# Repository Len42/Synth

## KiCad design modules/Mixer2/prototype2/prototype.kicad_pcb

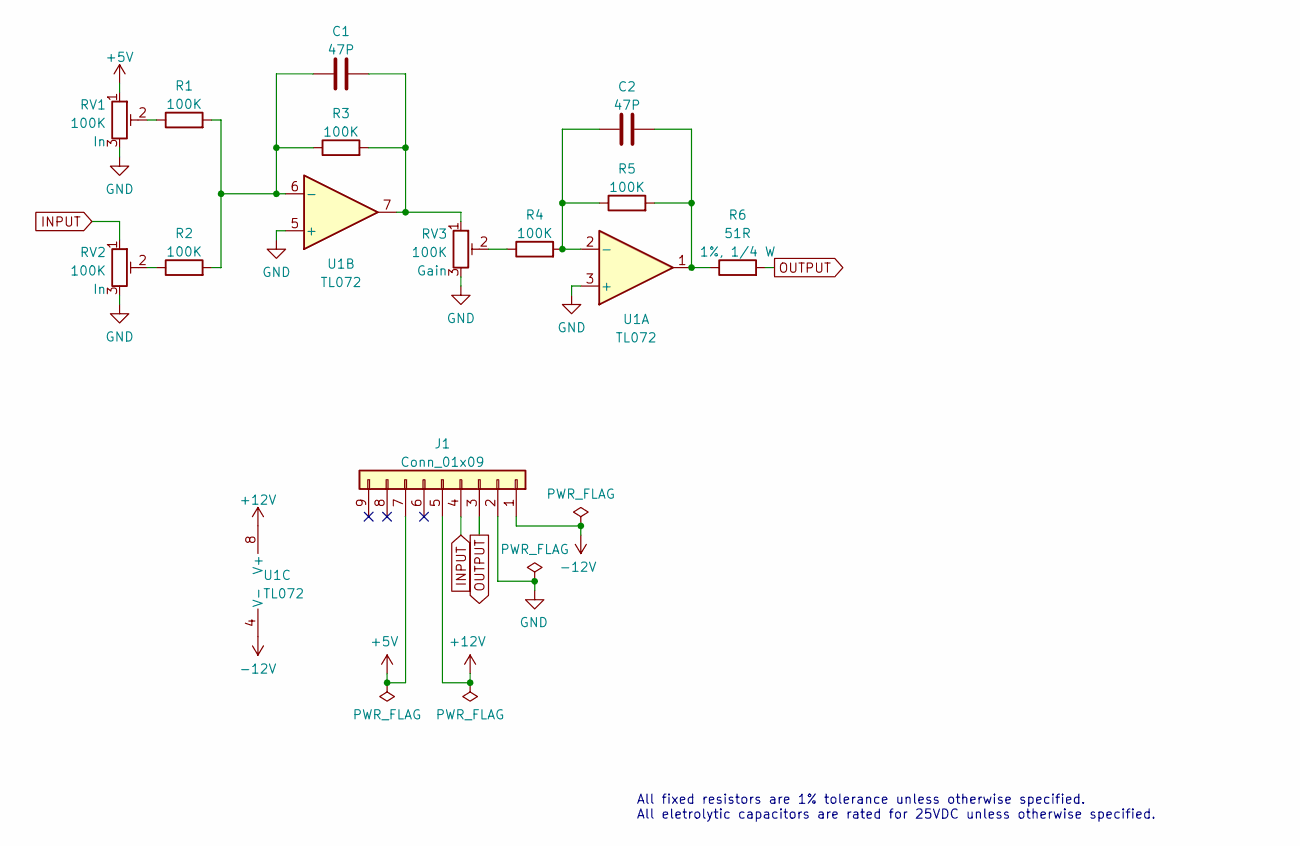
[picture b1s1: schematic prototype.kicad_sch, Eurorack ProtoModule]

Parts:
C1, C2: 47P; C_Disc_D5.0mm_W2.5mm_P2.50mm
J1: Conn_01x09; PinHeader_1x09_P2.54mm_Vertical
R1, R2, R3, R4, R5: 100K; R_Axial_DIN0207_L6.3mm_D2.5mm_P7.62mm_Horizontal; ManufacturerPartNum MFR-12*
R6: 51R; R_Axial_DIN0207_L6.3mm_D2.5mm_P10.16mm_Horizontal; ManufacturerPartNum MFR-25FBF52-51R
RV1, RV2, RV3: 100K; Potentiometer_Bourns_3386P_Top; ManufacturerPartNum 3386*
U1: TL072; DIP-8_W7.62mm; ManufacturerPartNum TL072BCP

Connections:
+5V: J1.7, RV1.1
+12V: J1.5, U1.8 (V+)
-12V: J1.1, U1.4 (V-)
GND: J1.2, RV1.3, RV2.3, RV3.3, U1.3 (+), U1.5 (+)
INPUT: J1.4, RV2.1
unnamed: C1.1, R1.2, R2.2, R3.1, U1.6 (-)
unnamed: C1.2, R3.2, RV3.1, U1.7
unnamed: C2.1, R4.2, R5.1, U1.2 (-)
unnamed: C2.2, R5.2, R6.1, U1.1
unnamed: R1.1, RV1.2
unnamed: R2.1, RV2.2
unnamed: R4.1, RV3.2
OUTPUT: J1.3, R6.2

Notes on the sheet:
All fixed resistors are 1% tolerance unless otherwise specified. All eletrolytic capacitors are rated for 25VDC unless otherwise specified.

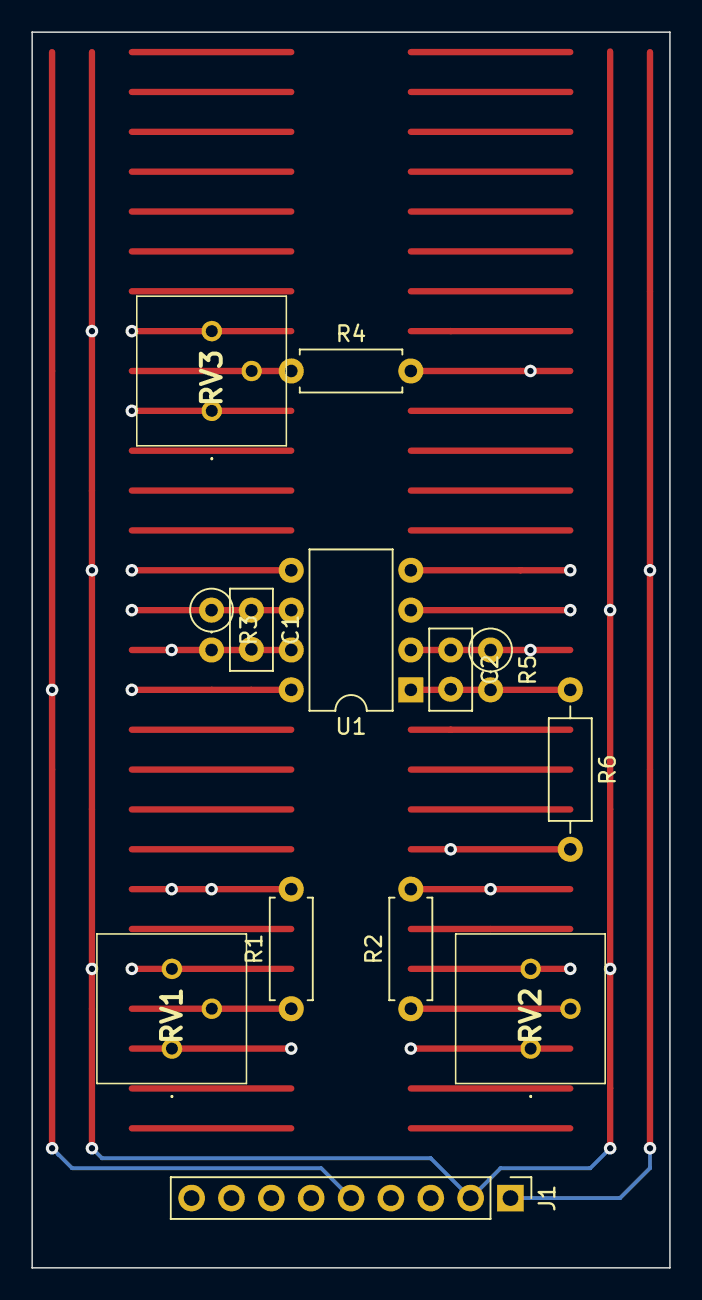
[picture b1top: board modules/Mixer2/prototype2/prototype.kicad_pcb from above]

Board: 6 copper layers, 40.6 x 78.7 mm, 13 parts (0 on the bottom side), 13 nets.

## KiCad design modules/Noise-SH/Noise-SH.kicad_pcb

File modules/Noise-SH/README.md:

# Noise / Sample & Hold

## 4HP Eurorack Module

### Features
- White and pink(ish) noise output
- Sample-and-hold with variable slew rate
- S&H can be triggered by an internal clock or external input
- Internal clock is output on the trigger jack when selected

### Notes

This module is built using the [Delptronics Module Construction Set](https://delptronics.com/module-construction-set.php) which includes PCBs for the front panel controls and other components. The PCB layout file is just a guide showing how I placed the components on the Delptronics boards. (It's a bit of a mess - sorry!)

Please note that I am a hobbyist, not a trained electronics engineer. No guarantees!

### Acknowledgements

[synthnerd](https://synthnerd.wordpress.com/2020/03/09/synth-diy-a-white-noise-generator/)

[Mutable Instruments](https://mutable-instruments.net/modules/kinks/open_source/)

### Software Used

[KiCad](https://www.kicad.org/) 5.1.10-1

<hr /><div><div style="float:left; padding-right:10px;"></div><div style="padding-left:10px;">© 2022 Len Popp<br />This work is licensed under a <a rel="license" href="http://creativecommons.org/licenses/by-sa/4.0/">Creative Commons Attribution-ShareAlike 4.0 International License</a>.</div></div>

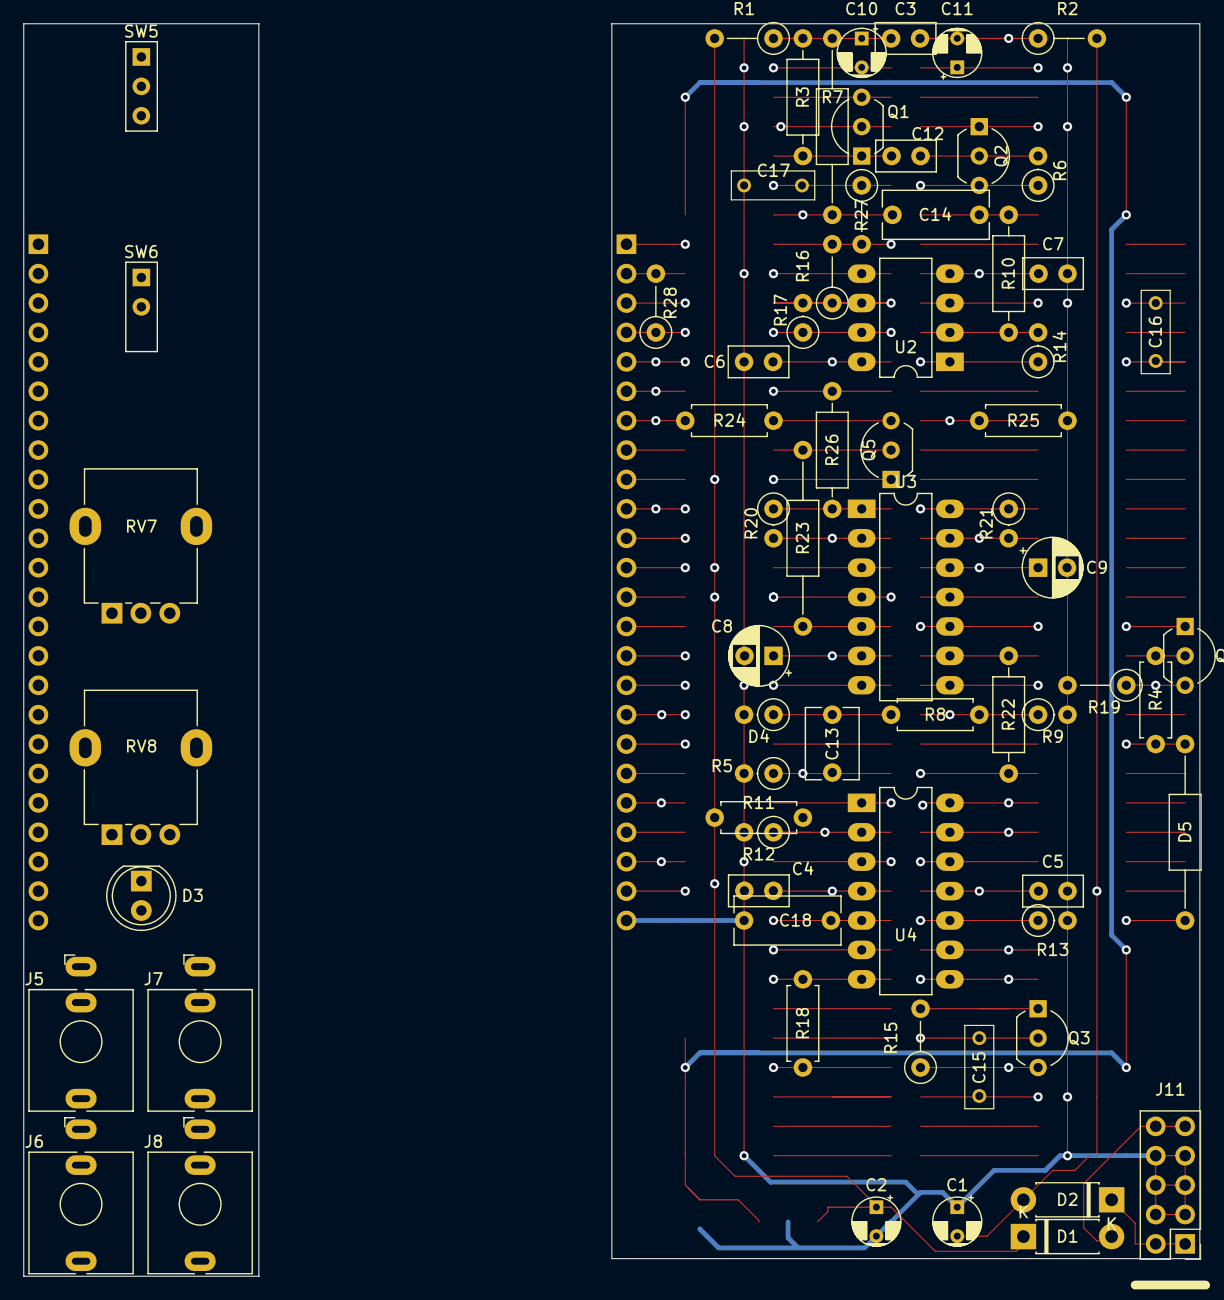
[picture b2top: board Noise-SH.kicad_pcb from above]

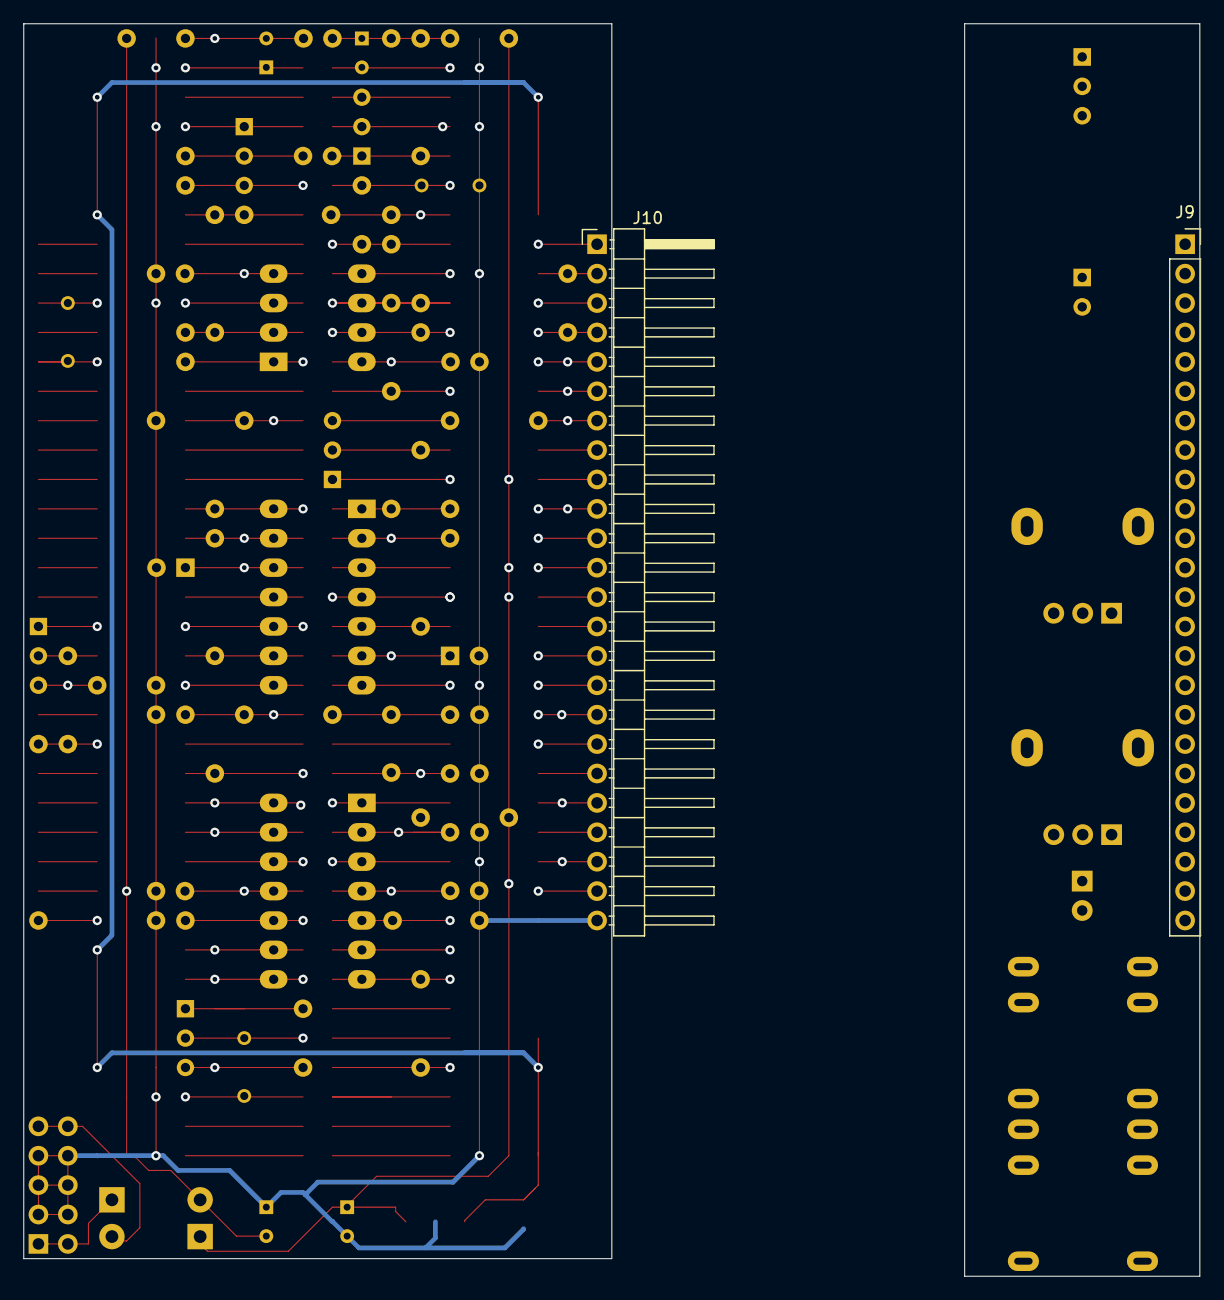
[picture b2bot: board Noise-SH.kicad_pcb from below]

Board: 6 copper layers, 50.8 x 106.7 mm, 70 parts (2 on the bottom side), 61 nets.

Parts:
C1, C2, C10, C11: 10U; CP_Radial_D4.0mm_P2.50mm
C3, C4, C5, C6, C7, C12: 100N; C_Disc_D5.0mm_W2.5mm_P2.50mm
C8: 4U7; CP_Radial_D5.0mm_P2.50mm
C9: 1U; CP_Radial_D5.0mm_P2.50mm
C13: 100P; C_Disc_D6.0mm_W4.4mm_P5.00mm
C14, C18: 1U; C_Rect_L9.0mm_W4.0mm_P7.50mm_MKT
C15, C16: 10N; C_Rect_Kemet_L7.2mm_W2.5mm_P5mm
C17: 1N; C_Rect_Kemet_L7.2mm_W2.5mm_P5mm
D1, D2: MBR150; D_DO-41_SOD81_P7.62mm_Horizontal
D3: LED_5mm_Blue; LED_D5.0mm
D4: 1N4148; SB_Gen_1
D5: 1N4148; SB_Gen_6
J5, J6, J7, J8: WQP-PJ398SM; Jack_3.5mm_QingPu_WQP-PJ398SM_Vertical
J9: Conn_Front; PinSocket_Delptronics_Front
J10: Conn__Back; PinHeader_Delptronics_Back_Left_4HP
J11: Eurorack_10; PinHeader-Eurorack-10-TH
Q1, Q2: 2N3904; TO-92_Inline_Wide
Q3: J309; TO-92_Inline_Wide
Q4, Q5: 2N3906; TO-92_Inline_Wide
R1, R2: 10R; SB_Gen_2
R3: 220K; R_Axial_DIN0207_L6.3mm_D2.5mm_P10.16mm_Horizontal
R4: 10K; R_Axial_DIN0207_L6.3mm_D2.5mm_P7.62mm_Horizontal
R5, R14: 100K; SB_Gen_1
R6, R13: 1M; SB_Gen_1
R7: 4K7; SB_Gen_6
R8: 11K; R_Axial_DIN0207_L6.3mm_D2.5mm_P7.62mm_Horizontal
R9: 330K; SB_Gen_1
R10: 15K; SB_Gen_4
R11: 1M; R_Axial_DIN0207_L6.3mm_D2.5mm_P7.62mm_Horizontal
R12: 120K; SB_Gen_1
R15: 1M; SB_Gen_2
R16, R19: 10K; SB_Gen_2
R17: 10K; SB_Gen_1
R18: 1K; R_Axial_DIN0207_L6.3mm_D2.5mm_P7.62mm_Horizontal
R20: 1K5; SB_Gen_1
R21: 82K; SB_Gen_1
R22: 2K2; R_Axial_DIN0207_L6.3mm_D2.5mm_P10.16mm_Horizontal
R23: 10K; SB_Gen_6
R24: 6K2; R_Axial_DIN0207_L6.3mm_D2.5mm_P7.62mm_Horizontal
R25: 13K; R_Axial_DIN0207_L6.3mm_D2.5mm_P7.62mm_Horizontal
R26: 4K7; R_Axial_DIN0207_L6.3mm_D2.5mm_P10.16mm_Horizontal
R27: 3K9; SB_Gen_2
R28: 1K; SB_Gen_2
RV7, RV8: 1M; Potentiometer_Alpha_RD901F-40-00D_Single_Vertical
SW5: ON_ON; SW_SPDT_THT_2.54
SW6: SPST; SW_SPST_THT_2.54
U2: TL072; DIP-8_W7.62mm_LongPads
U3: ICM7556; DIP-14_W7.62mm_LongPads
U4: TL074; DIP-14_W7.62mm_LongPads

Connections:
+12VA: C3.1, C6.1, C10.1, R1.1, R3.1, R7.1, U2.8
-12V: C1.2, C5.2, D1.2, R2.2, U4.11
-12VA: C3.2, C7.2, C11.2, R2.1, U2.4
/Main/TRIGGER: D5.1, R4.2, U4.1
IN-SAMPLE: J10.5, R13.1, U4.10
INOUT-TRIG: C13.2, J10.6, J10.15, R5.1
LED-TRIG-A: J10.23, R22.1
LED-TRIG-C: C1.1, C2.2, C4.2, C5.1, C6.2, C7.1, C8.2, C9.2, C10.2, C11.1, C15.2, C17.2, C18.1, D4.2, J5.S, J6.S, J7.S, J8.S, J9.24, J10.22, J10.24, J11.3, J11.4, J11.5, J11.6, J11.7, J11.8, Q1.2, Q2.1, R5.2, R9.2, R12.2, R13.2, R19.2, R25.2, U2.3, U2.5, U3.7
NOISE-SELECT: J10.2, R28.2
unnamed: C8.1, R20.2, U3.2, U3.6
unnamed: C9.1, R21.2, U3.12, U3.13
unnamed: C12.1, Q2.2, R6.2
unnamed: C12.2, Q1.1, R3.2
unnamed: C13.1, D4.1, R8.2
unnamed: C14.1, R10.2
unnamed: C14.2, Q2.3, R6.1, R7.2
unnamed: C15.1, Q3.2, U4.12
unnamed: C16.2, R16.1, R17.2, U2.6
unnamed: D1.1, J11.1, J11.2
unnamed: D2.2, J11.9, J11.10
unnamed: D3.1, J9.22
unnamed: D3.2, J9.23
unnamed: D5.2, Q3.3, R15.1
unnamed: J5.T, J9.5
unnamed: J5.TN, J9.4
unnamed: J6.T, J9.10
unnamed: J7.T, J9.15
unnamed: J8.T, J9.20
unnamed: J9.1, SW5.3
unnamed: J9.2, SW5.2
unnamed: J9.3, SW5.1
unnamed: J9.6, SW6.1
unnamed: J9.7, SW6.2
unnamed: J9.11, RV7.3
unnamed: J9.12, RV7.2
unnamed: J9.13, RV7.1
unnamed: J9.16, RV8.3
unnamed: J9.17, RV8.2
unnamed: J9.18, RV8.1
unnamed: Q3.1, R15.2, U4.8, U4.9
unnamed: Q4.2, R4.1
unnamed: Q4.3, R19.1, U3.8
unnamed: Q5.2, R23.1
unnamed: Q5.3, R24.1
unnamed: R8.1, R9.1, U4.3
unnamed: R10.1, R14.2, U2.2
unnamed: R11.2, R12.1, U4.2
unnamed: R14.1, R16.2, R27.2, U2.1
unnamed: R18.2, U4.6, U4.7
unnamed: R20.1, R26.2, U3.1
unnamed: R22.2, U3.9
unnamed: R23.2, U3.5
OUT-CLOCK-TRIG: J10.7, R24.2, R25.1
OUT-HOLD: J10.10, R18.1
OUT-NOISE: J10.4, J10.20, R28.1
OUT-NOISE-PINK: C16.1, J10.1, R17.1, U2.7
OUT-NOISE-WHITE: C17.1, J10.3, R27.1
RV-CLOCK-FREQ-1: C2.1, C4.1, D2.1, J10.12, Q4.1, Q5.1, R1.2, R11.1, R21.1, U3.4, U3.10, U3.14, U4.4
RV-CLOCK-FREQ-2: J10.11, R26.1
RV-SLEW-1: J10.18, U4.13, U4.14
RV-SLEW-2: C18.2, J10.16, J10.17, U4.5

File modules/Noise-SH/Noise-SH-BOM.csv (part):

Ref,Qty,Name,Value,Value2,Note,Description,Datasheet,Manufacturer,ManuPartNum,Distributor1,DistributorPartNum1,DistributorPartLink1,Distributor2,DistributorPartNum2,DistributorPartLink2,Distributor3,DistributorPartNum3,DistributorPartLink3
"C1 C2 C10 C11","4","CP_10U","10U","25 VDC","","Capacitor - Electrolytic - 12 V decoupling","https://industrial.panasonic.com/cdbs/www-data/pdf/RDF0000/A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","Panasonic","EEA-FC1E100","Mouser","667-EEA-FC1E100","https://www.mouser.ca/ProductDetail/Panasonic/EEA-FC1E100?qs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"
"C3 C4 C5 C6 C7","5","CC_100N","100N","","IC decoupling","Capacitor - Ceramic - IC decoupling","https://product.tdk.com/system/files/dam/doc/product/capacit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","TDK","FG18X7R1H104KNT06","Mouser","810-FG18X7R1H104KNT6","https://www.mouser.ca/ProductDetail/810-FG18X7R1H104KNT6"
"C8","1","CP","4U7","","","Capacitor - Electrolytic","https://www.mouser.ca/datasheet/2/977/e_YXJ-1601195.pdf","Rubycon","50YXJ1M5X11","Mouser","232-50YXJ1M5X11","https://www.mouser.ca/ProductDetail/232-50YXJ1M5X11"
"C9","1","CP","1U","","","Capacitor - Electrolytic","https://www.mouser.ca/datasheet/2/977/e_YXJ-1601195.pdf","Rubycon","50YXJ1M5X11","Mouser","232-50YXJ1M5X11","https://www.mouser.ca/ProductDetail/232-50YXJ1M5X11"
"C12","1","C","100N","C0G/NP0","","Capacitor - Unpolarized","https://product.tdk.com/system/files/dam/doc/product/capacit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","TDK","FA16C0G2A104JRU06","Mouser","810-FA16C0G2A104JRU6","https://www.mouser.ca/ProductDetail/TDK/FA16C0G2A104JRU06?qs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"
"C13","1","C","100P","","","Capacitor - Unpolarized","https://www.mouser.com/catalog/specsheets/tdkc-s-a0002934059-1.pdf","TDK","CK45-R3AD101K-NRA","Mouser","810-CK45-R3AD101K-NA","https://www.mouser.ca/ProductDetail/TDK/CK45-R3AD101K-NRA?qs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"
"C14 C18","2","C","1U","","","Capacitor - Unpolarized","https://product.tdk.com/system/files/dam/doc/product/capacit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","TDK","B32560J0105K000","Mouser","871-B32560J105K","https://www.mouser.ca/ProductDetail/EPCOS-TDK/B32560J0105K00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"
"C15 C16","2","CF","10N","","","Capacitor - Film","https://www.mouser.ca/datasheet/2/212/1/KEM_F3072_SMR-1103375.pdf","KEMET","SMR5103J50J01L16.5CBULK","Mouser","80-SMR5103J50J0116","https://www.mouser.ca/ProductDetail/?qs=lyRJTFulC0ZVzsb1DGnF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"
"C17","1","CF","1N","","","Capacitor - Film","https://www.mouser.ca/datasheet/2/212/F3294_MMK-1101858.pdf","KEMET","MMK5102J100J01L16.5TA18","Mouser","80-MMK5102J100J1TA18","https://www.mouser.ca/ProductDetail/80-MMK5102J100J1TA18"
"D1 D2","2","MBR150","MBR150","","","Schottky rectifier diode","https://www.onsemi.com/pdf/datasheet/mbr150-d.pdf","On Semi","MBR150RLG","Mouser","863-MBR150RLG","https://www.mouser.ca/ProductDetail/ON-Semiconductor/MBR150R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"
"D3","1","LED_5mm_Blue","LED_5mm_Blue","","","Blue Light Emitting Diode","https://www.mouser.ca/datasheet/2/423/VAOL-5LSBY1-1064871.pdf","VCC","VAOL-5LSBY1","Mouser","593-VAOL-5LSBY1","https://www.mouser.ca/ProductDetail/VCC/VAOL-5LSBY1?qs=sGAEp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"
"D4 D5","2","1N4148","1N4148","","","Switching diode, 100V 0.15A, DO-35","https://www.mouser.ca/datasheet/2/308/1N914_D-2309448.pdf","On Semi / Fairchild","1N4148-T50R","Mouser","512-1N4148T50R","https://www.mouser.ca/ProductDetail/?qs=0lQeLiL1qyZS6rosZp7E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"
"H1","1","PCB_Delptronics_MCS_4HP","PCB_Delptronics_MCS_4HP","","PCB & panel kit","Delptronics Module Construction Set - 4HP PCB & panel kit","https://delptronics.com/module-construction-set.php","Delptronics","","Delptronics","","https://delptronics.com/module-construction-set.php","synthCube","DELPMCSMSTR","https://synthcube.com/cart/delptronics-module-construction-set","Modular Addict","","https://modularaddict.com/module-construction-set-eurorack-p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"
"J5 J6 J7 J8","4","Jack_WQP-PJ398","WQP-PJ398SM","","","Audio Jack, 2 Poles (Mono / TS), Switched T Pole (Normalling), QingPu / Thonkiconn","http://www.qingpu-electronics.com/en/products/WQP-PJ398SM-362.html","QingPu / Thonk","PJ398SM / WQP518MA","Thonk","PJ398SM","https://www.thonk.co.uk/shop/thonkiconn/","SynthCube","WQP518MA","https://synthcube.com/cart/3-5mm-euro-jacks","Adafruit","4031","https://www.adafruit.com/product/4031"
"Q1 Q2","2","Q_NPN_2N3904","2N3904","","","Small Signal NPN Transistor, 0.2A Ic, 40V Vce, TO-92","https://www.onsemi.com/pub/Collateral/2N3903-D.PDF","Central Semiconductor","2N3904 PBFREE","Mouser","610-2N3904","https://www.mouser.ca/ProductDetail/Central-Semiconductor/2N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"
"Q3","1","Q_JFET_N_SDG","J309","","","N-JFET transistor, source/drain/gate","https://www.mouser.ca/datasheet/2/676/jfet-j308-j309-j310-in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","InterFET","J309","Mouser","106-J309","https://www.mouser.ca/ProductDetail/InterFET/J309?qs=%2Fha2p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"
"Q4 Q5","2","Q_PNP_2N3906","2N3906","","","Small Signal PNP Transistor, -0.2A Ic, -40V Vce, TO-92","https://www.onsemi.com/pub/Collateral/2N3906-D.PDF","ON Semiconductor / Fairchild","2N3906TAR","Mouser","512-2N3906TAR","https://www.mouser.ca/ProductDetail/ON-Semiconductor-Fairchi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"
"R1 R2","2","R","10R","","","Resistor","https://www.mouser.ca/datasheet/2/447/Yageo_LR_MFR_1-1714151.pdf","Mouser","MFR-25FTF52-10R","Mouser","603-MFR-25FTF52-10R","https://www.mouser.ca/ProductDetail/YAGEO/MFR-25FTF52-10R?qs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"
"R3","1","R","220K","","","Resistor","https://www.mouser.ca/datasheet/2/447/Yageo_LR_MFR_1-1714151.pdf","YAGEO","MFR-25FTF52-220K","Mouser","603-MFR-25FTF52-220K","https://www.mouser.ca/ProductDetail/?qs=iCzJi%2FIZBF5PYwecy8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"
"R4 R16 R17 R19 R23","5","R","10K","","","Resistor","https://www.mouser.ca/datasheet/2/447/Yageo_LR_MFR_1-1714151.pdf","YAGEO","MFR-12FRF52-10K","Mouser","603-MFR-12FRF5210K","https://www.mouser.ca/ProductDetail/?qs=19cKSROHwrBLAZVjkXso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"
"R5 R14","2","R","100K","","","Resistor","https://www.mouser.ca/datasheet/2/447/Yageo_LR_MFR_1-1714151.pdf","YAGEO","MFR-12FTF52-100K","Mouser","603-MFR-12FTF52-100K","https://www.mouser.ca/ProductDetail/YAGEO/MFR-12FTF52-100K?q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"
"R6 R11 R13 R15","4","R","1M","","","Resistor","https://www.mouser.ca/datasheet/2/447/Yageo_LR_MFR_1-1714151.pdf","YAGEO","MFR-12FTF52-1M","Mouser","603-MFR-12FTF52-1M","https://www.mouser.ca/ProductDetail/YAGEO/MFR-12FTF52-1M?qs=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"
"R7 R26","2","R","4K7","","","Resistor","https://www.mouser.ca/datasheet/2/447/Yageo_LR_MFR_1-1714151.pdf","YAGEO","MFR-12FTF52-4K7","Mouser","603-MFR-12FTF52-4K7","https://www.mouser.ca/ProductDetail/YAGEO/MFR-12FTF52-4K7?qs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"
"R8","1","R","11K","","","Resistor","https://www.mouser.ca/datasheet/2/447/Yageo_LR_MFR_1-1714151.pdf","YAGEO","MFR-12FTF52-11K","Mouser","603-MFR-12FTF52-11K","https://www.mouser.ca/ProductDetail/YAGEO/MFR-12FTF52-11K?qs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"
"R9","1","R","330K","","","Resistor","https://www.mouser.ca/datasheet/2/447/Yageo_LR_MFR_1-1714151.pdf","YAGEO","MFR-12FTF52-100K","Mouser","603-MFR-12FTF52-100K","https://www.mouser.ca/ProductDetail/YAGEO/MFR-12FTF52-100K?q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"
"R10","1","R","15K","","","Resistor","https://www.mouser.ca/datasheet/2/447/Yageo_LR_MFR_1-1714151.pdf","YAGEO","MFR-12FTF52-24K","Mouser","603-MFR-12FTF52-24K","https://www.mouser.ca/ProductDetail/YAGEO/MFR-12FTF52-24K?qs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"
"R12","1","R","120K","","","Resistor","https://www.mouser.ca/datasheet/2/447/Yageo_LR_MFR_1-1714151.pdf","YAGEO","MFR-25FTE52-15K","Mouser","603-MFR-25FTE52-15K","https://www.mouser.ca/ProductDetail/YAGEO/MFR-25FTE52-15K?qs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"
"R18 R28","2","R_1K_Output","1K","5%, 1/4 W","Output limiting","Resistor","https://www.mouser.ca/datasheet/2/427/ccf07-1762725.pdf","Vishay / Dale","CCF071K00JKE36","Mouser","71-CCF071K00JKE36","https://www.mouser.ca/ProductDetail/Vishay-Dale/CCF071K00JKE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"
"R20","1","R","1K5","","","Resistor","https://www.mouser.ca/datasheet/2/447/Yageo_LR_MFR_1-1714151.pdf","YAGEO","MFR-12*","Mouser","603-MFR-12*","https://www.mouser.ca/c/?m=YAGEO&power+rating=166+mW+(1%2f6+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"
"R21","1","R","82K","","","Resistor","https://www.mouser.ca/datasheet/2/447/Yageo_LR_MFR_1-1714151.pdf","YAGEO","MFR-12*","Mouser","603-MFR-12*","https://www.mouser.ca/c/?m=YAGEO&power+rating=166+mW+(1%2f6+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"
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
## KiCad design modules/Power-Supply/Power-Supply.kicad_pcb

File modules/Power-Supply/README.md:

# Eurorack Power Supply

This is the power supply that I made for my Eurorack modular system. It is meant to live inside the system case with the power switch and DC input jack mounted on the side of the case.

### Specs

Input: Requires between 9 V and 36 V DC, 35W (from a power brick / wall wart / laptop charger)

Output: +12 V, -12 V (1 A each), +5 V (500 mA)

### Notes

I used an old laptop charger as the AC-DC converter (power brick) so I didn't have to mess around with mains voltage. The required Eurorack voltages (+12 V, -12 V, +5 V) are supplied by switching DC-DC converters. The outputs are isolated from the input.

There are two 16-pin Eurorack power connectors; you'll want a busboard or flying-bus cable to feed multiple modules.

The power supply is assembled on a stripboard PCB. I have provided a layout diagram.

Please note that I am a hobbyist, not a trained electronics engineer. No guarantees!

### Software Used

[KiCad](https://www.kicad.org/) 6.0.0

<hr /><br />© 2022 Len Popp CC BY<br />This work is licensed under a <a rel="license" href="http://creativecommons.org/licenses/by/4.0/">Creative Commons Attribution 4.0 International License</a>.

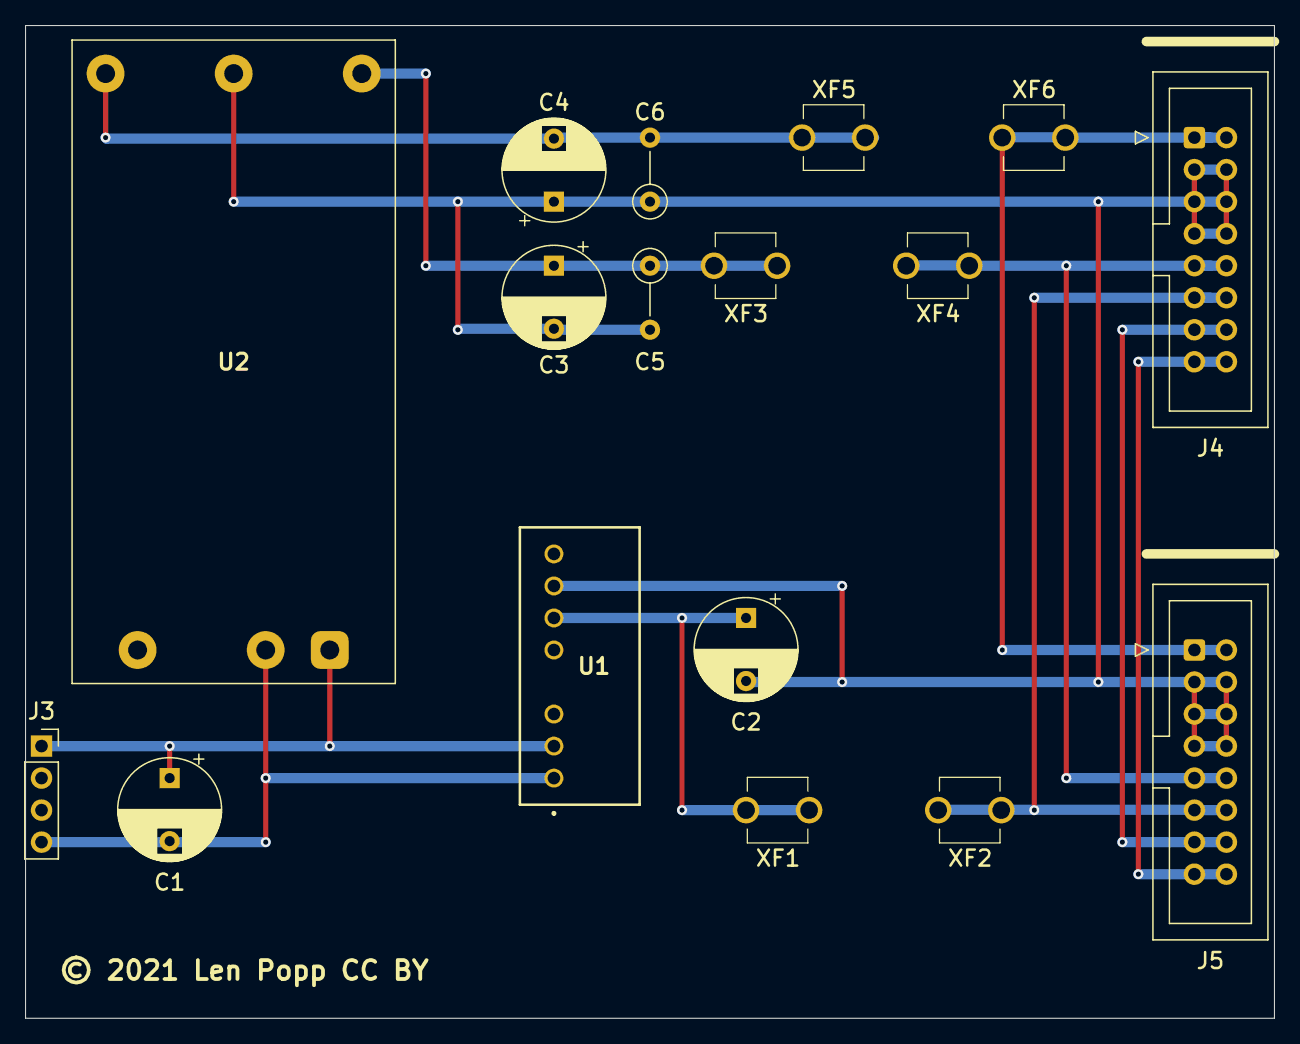
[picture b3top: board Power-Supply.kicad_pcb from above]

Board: 2 copper layers, 99.1 x 78.7 mm, 17 parts (0 on the bottom side), 11 nets.

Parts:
C1, C3, C4: 220U; CP_Radial_D8.0mm_P5.00mm
C2: 22U; CP_Radial_D8.0mm_P5.00mm
C5, C6: 100N; SB_Gen_2
J3: HDR_F; PinSocket_1x04_P2.54mm_Vertical
J4, J5: Conn_Eurorack_Pwr_16; IDC-Header-Eurorack-16-TH
U1: PRM3W-E12-S5-S; Converter_DCDC_CUI_PRM3W
U2: PYBE30-Q24-D12; Converter_DCDC_CUI_PYBE30
XF1, XF2, XF3, XF4, XF5, XF6: CLIP; FuseClip_D5mm_P5mm_52000001009

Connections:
+5V: J4.11 (+5V), J4.12, J5.11 (+5V), J5.12, XF2.1
+12V: J4.9 (+12V), J4.10, J5.9 (+12V), J5.10, XF4.1
-12V: J4.1 (-12V), J4.2, J5.1 (-12V), J5.2, XF6.1
GND: C2.2, C3.2, C4.1, C5.2, C6.1, J4.3 (GND), J4.4, J4.5 (GND), J4.6, J4.7 (GND), J4.8, J5.3 (GND), J5.4, J5.5 (GND), J5.6, J5.7 (GND), J5.8, U1.7 (0V), U2.5 (0V)
unnamed: C1.1, J3.1, U1.2 (+VIN), U2.1 (+VIN)
unnamed: C1.2, J3.4, U1.1 (-VIN), U2.2 (-VIN)
unnamed: C2.1, U1.6 (+VOUT), XF1.1
unnamed: C3.1, C5.1, U2.6 (+VOUT), XF3.1
unnamed: C4.2, C6.2, U2.4 (-VOUT), XF5.1
unnamed: J4.13 (CV), J4.14, J5.13 (CV), J5.14
unnamed: J4.15 (GATE), J4.16, J5.15 (GATE), J5.16

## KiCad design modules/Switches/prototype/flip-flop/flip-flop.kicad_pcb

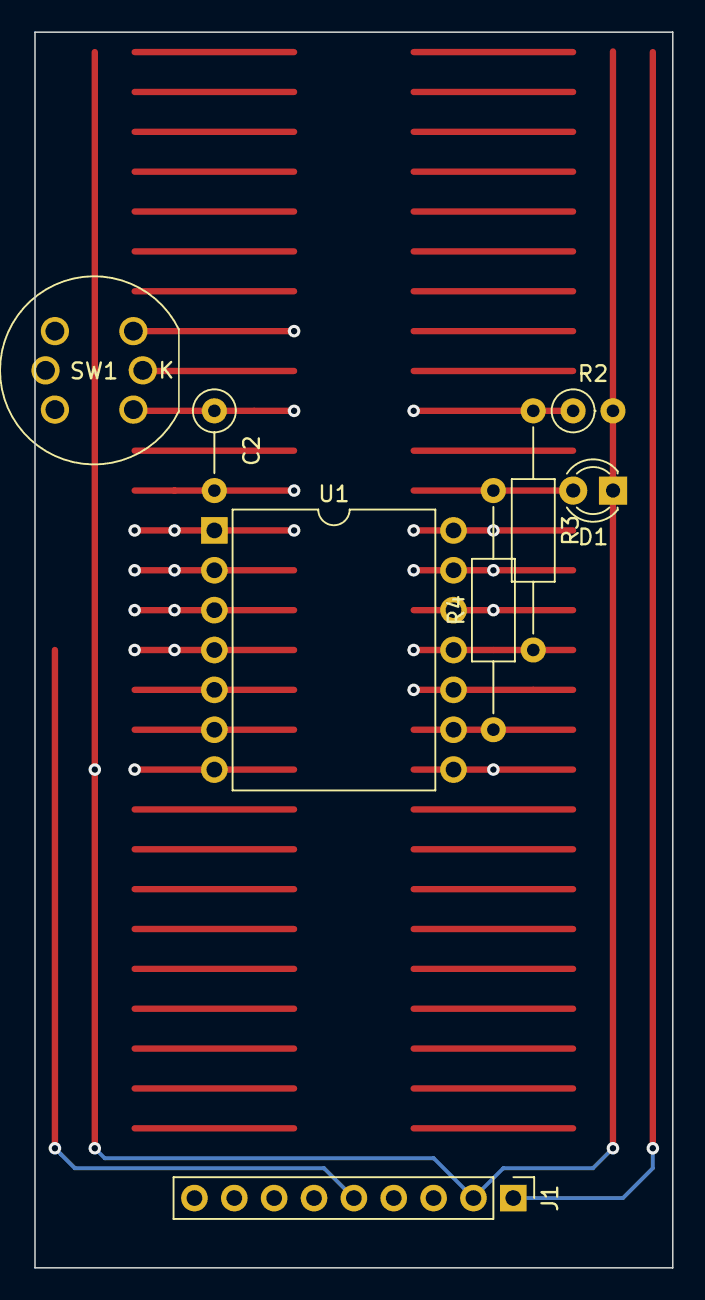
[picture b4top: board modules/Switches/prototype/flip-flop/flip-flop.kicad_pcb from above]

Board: 6 copper layers, 40.6 x 78.7 mm, 8 parts (0 on the bottom side), 7 nets.

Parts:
C2: 100N; SB_Gen_2
D1: LED; LED_D3.0mm_Clear
J1: Conn_01x09; PinHeader_1x09_P2.54mm_Vertical
R2: 10K; SB_Gen_1
R3: 10K; SB_Gen_6
R4: 1K; SB_Gen_6
SW1: SW_Push; SW_Push_LED_C&K_D6R
U1: SN74HCS74; Breakout_DIP-14_W15.24mm

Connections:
+5V: C2.1, J1.7, SW1.4, U1.1 (~R), U1.2 (D), U1.3 (C), U1.4 (~S), U1.10 (~S), U1.13 (~R), U1.14 (VDD)
GND: D1.1 (K), J1.2, R2.2, U1.7 (VSS)
unnamed: D1.2 (A), R4.2
unnamed: R2.1, R3.1, SW1.2
unnamed: C2.2, R3.2, U1.11 (C)
unnamed: U1.8 (~Q), U1.12 (D)
unnamed: R4.1, U1.9 (Q)

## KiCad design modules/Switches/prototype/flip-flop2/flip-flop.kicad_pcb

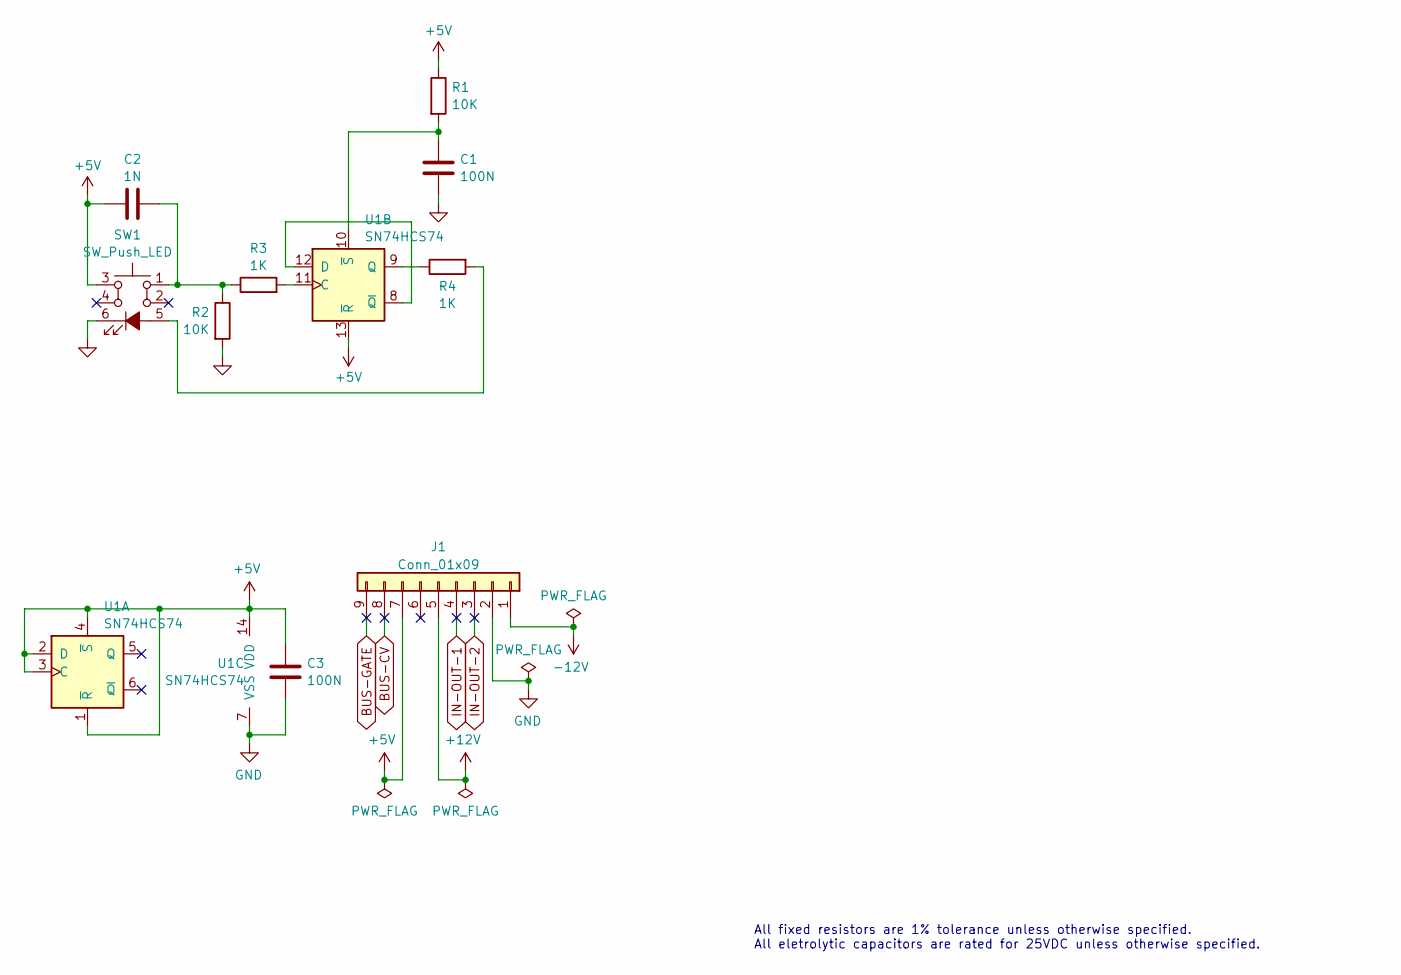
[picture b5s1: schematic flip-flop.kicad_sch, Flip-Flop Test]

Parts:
C1, C3: 100N; C_Disc_D5.0mm_W2.5mm_P2.50mm; ManufacturerPartNum FG18X7R1H104KNT06
C2: 1N; SB_Gen_2; ManufacturerPartNum FG18X7R1H104KNT06
J1: Conn_01x09; PinHeader_1x09_P2.54mm_Vertical
R1: 10K; R_Axial_DIN0207_L6.3mm_D2.5mm_P7.62mm_Horizontal; ManufacturerPartNum MFR-12*
R2: 10K; SB_Gen_1; ManufacturerPartNum MFR-12*
R3: 1K; SB_Gen_1; ManufacturerPartNum MFR-12*
R4: 1K; SB_Gen_1; ManufacturerPartNum CCF071K00JKE36
SW1: SW_Push_LED; SW_Push_LED_C&K_D6R; ManufacturerPartNum D6RLBUF1 LFS
U1: SN74HCS74; Breakout_DIP-14_W15.24mm; ManufacturerPartNum SN74HCS74DR

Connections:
+5V: C2.1, C3.1, J1.7, R1.1, SW1.3, U1.1 (~R), U1.2 (D), U1.3 (C), U1.4 (~S), U1.13 (~R), U1.14 (VDD)
+12V: J1.5
-12V: J1.1
BUS-CV: J1.8
BUS-GATE: J1.9
GND: C1.2, C3.2, J1.2, R2.2, SW1.6 (K), U1.7 (VSS)
IN-OUT-1: J1.4
IN-OUT-2: J1.3
unnamed: C2.2, R2.1, R3.1, SW1.1
unnamed: R4.2, SW1.5 (A)
unnamed: R3.2, U1.11 (C)
unnamed: U1.8 (~Q), U1.12 (D)
unnamed: R4.1, U1.9 (Q)
unnamed: C1.1, R1.2, U1.10 (~S)

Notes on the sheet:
All fixed resistors are 1% tolerance unless otherwise specified. All eletrolytic capacitors are rated for 25VDC unless otherwise specified.

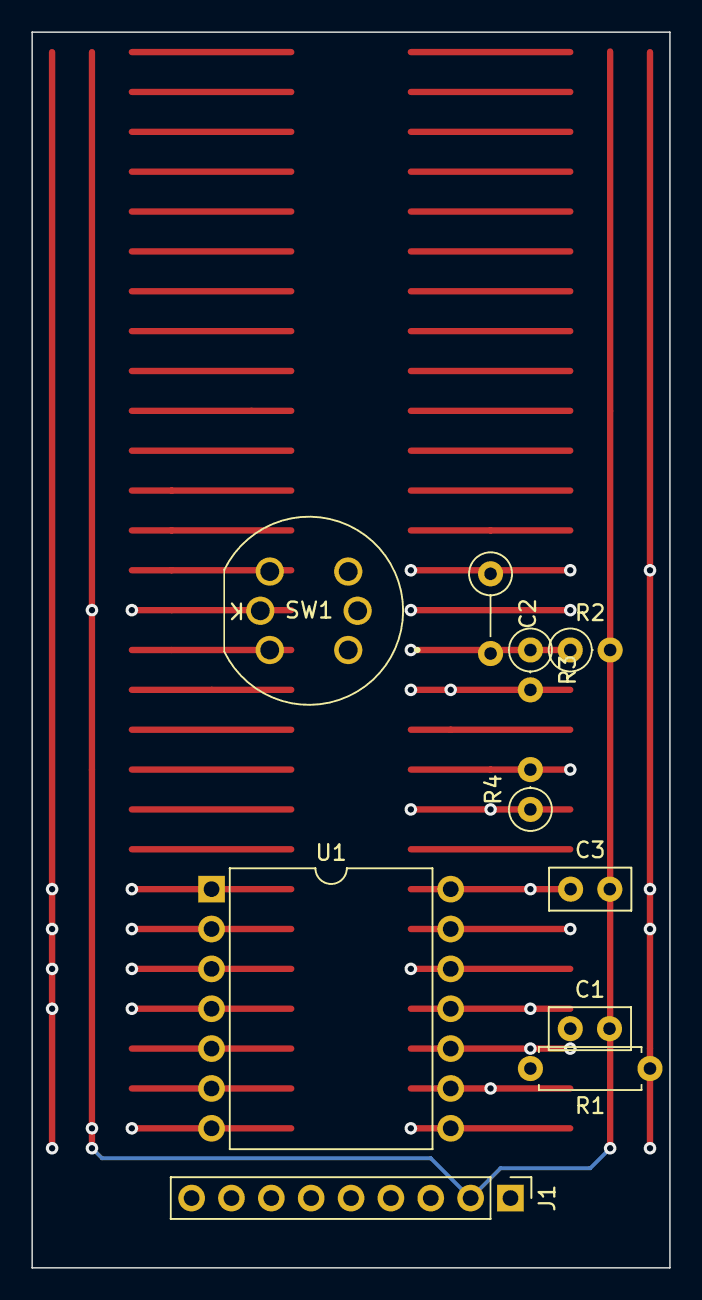
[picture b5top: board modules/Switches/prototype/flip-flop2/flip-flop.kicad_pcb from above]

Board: 6 copper layers, 40.6 x 78.7 mm, 10 parts (0 on the bottom side), 8 nets.

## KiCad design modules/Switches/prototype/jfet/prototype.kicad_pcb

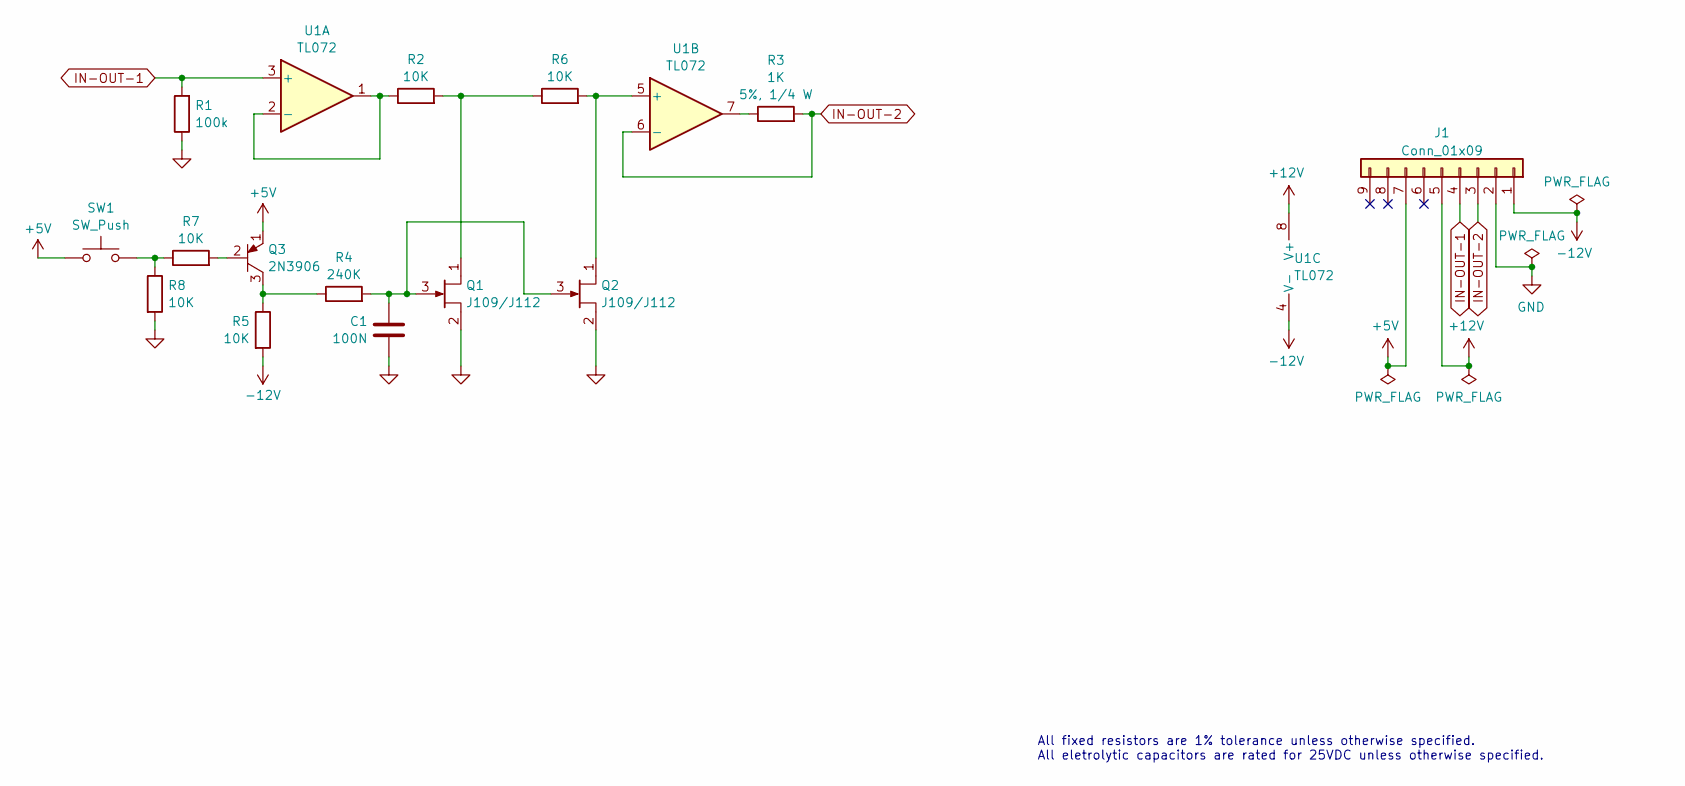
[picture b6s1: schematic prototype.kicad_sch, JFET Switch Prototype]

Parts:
C1: 100N; C_Disc_D5.0mm_W2.5mm_P2.50mm; ManufacturerPartNum FG18X7R1H104KNT06
J1: Conn_01x09; PinHeader_1x09_P2.54mm_Vertical
Q1, Q2: J109/J112; TO-92_Inline_Wide
Q3: 2N3906; TO-92_Inline_Wide; ManufacturerPartNum 2N3906TAR
R1: 100k; SB_Gen_1; ManufacturerPartNum MFR-12*
R2, R6: 10K; R_Axial_DIN0207_L6.3mm_D2.5mm_P7.62mm_Horizontal; ManufacturerPartNum MFR-12*
R3: 1K; SB_Gen_2; ManufacturerPartNum CCF071K00JKE36
R4: 240K; SB_Gen_2; ManufacturerPartNum MFR-12*
R5, R7, R8: 10K; SB_Gen_2; ManufacturerPartNum MFR-12*
SW1: SW_Push; SW_PUSH_6mm_2; ManufacturerPartNum FSM4JRT
U1: TL072; DIP-8_W7.62mm; ManufacturerPartNum TL072BCP

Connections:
+5V: J1.7, Q3.1 (E), SW1.1
+12V: J1.5, U1.8 (V+)
-12V: J1.1, R5.2, U1.4 (V-)
GND: C1.2, J1.2, Q1.2 (S), Q2.2 (S), R1.1, R8.2
IN-OUT-1: J1.4, R1.2, U1.3 (+)
IN-OUT-2: J1.3, R3.2, U1.6 (-)
unnamed: Q1.1 (D), R2.2, R6.1
unnamed: C1.1, Q1.3 (G), Q2.3 (G), R4.2
unnamed: Q2.1 (D), R6.2, U1.5 (+)
unnamed: Q3.2 (B), R7.2
unnamed: Q3.3 (C), R4.1, R5.1
unnamed: R3.1, U1.7
unnamed: R7.1, R8.1, SW1.2
unnamed: R2.1, U1.1, U1.2 (-)

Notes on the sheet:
All fixed resistors are 1% tolerance unless otherwise specified. All eletrolytic capacitors are rated for 25VDC unless otherwise specified.

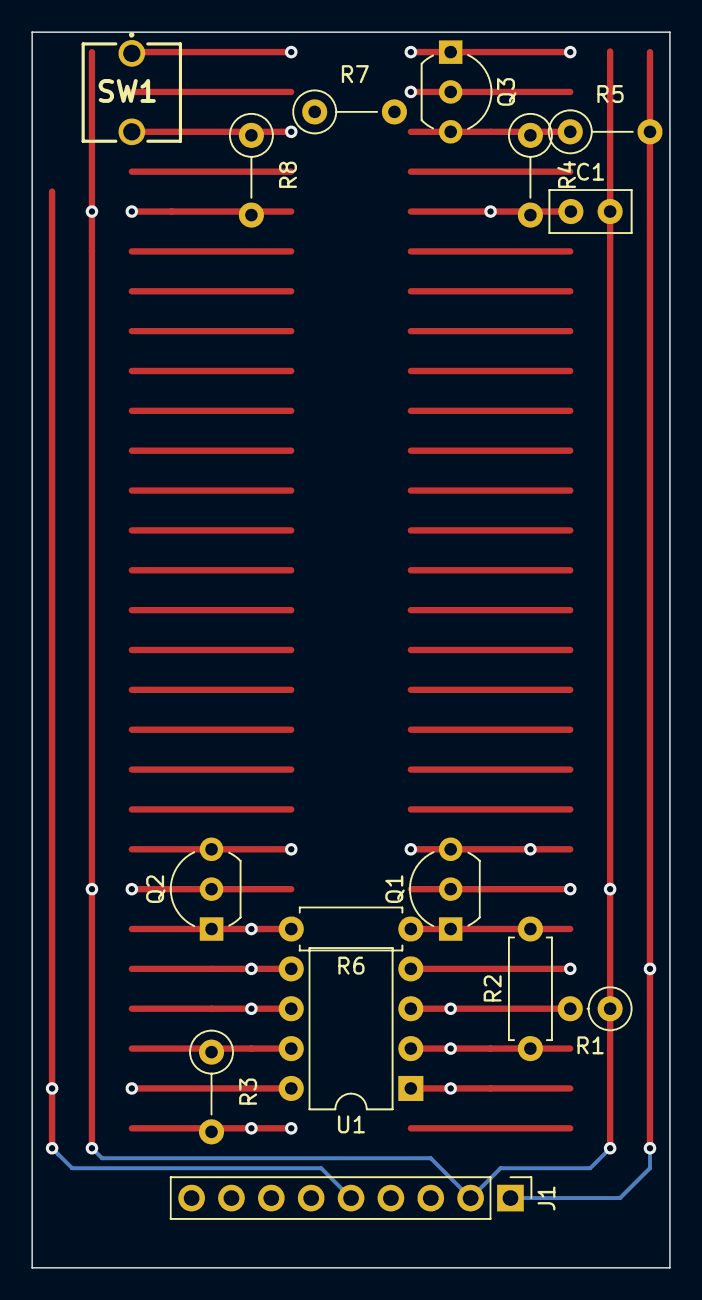
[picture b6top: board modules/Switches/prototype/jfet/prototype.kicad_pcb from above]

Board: 6 copper layers, 40.6 x 78.7 mm, 15 parts (0 on the bottom side), 14 nets.

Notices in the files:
modules/Mixer2/prototype1/prototype.kicad_sch:
Copyright © 2022 Len Popp CC BY
modules/Noise-SH/Noise-SH.kicad_pcb:
Copyright © 2021 Len Popp CC BY-SA
modules/Switches/prototype/fake-vactrol/prototype.kicad_sch:
Copyright © 2023 Len Popp CC BY
